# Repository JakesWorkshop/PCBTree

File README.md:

# PCBTree
A blinking Christmas Tree you can solder yourself

Tannenbaum.zip contains all Gerber files you'll need packed together into one 100 by 100 mm PCB. 
Note that this PCB contains 3 different desigs and some fabricators will charge extra for this

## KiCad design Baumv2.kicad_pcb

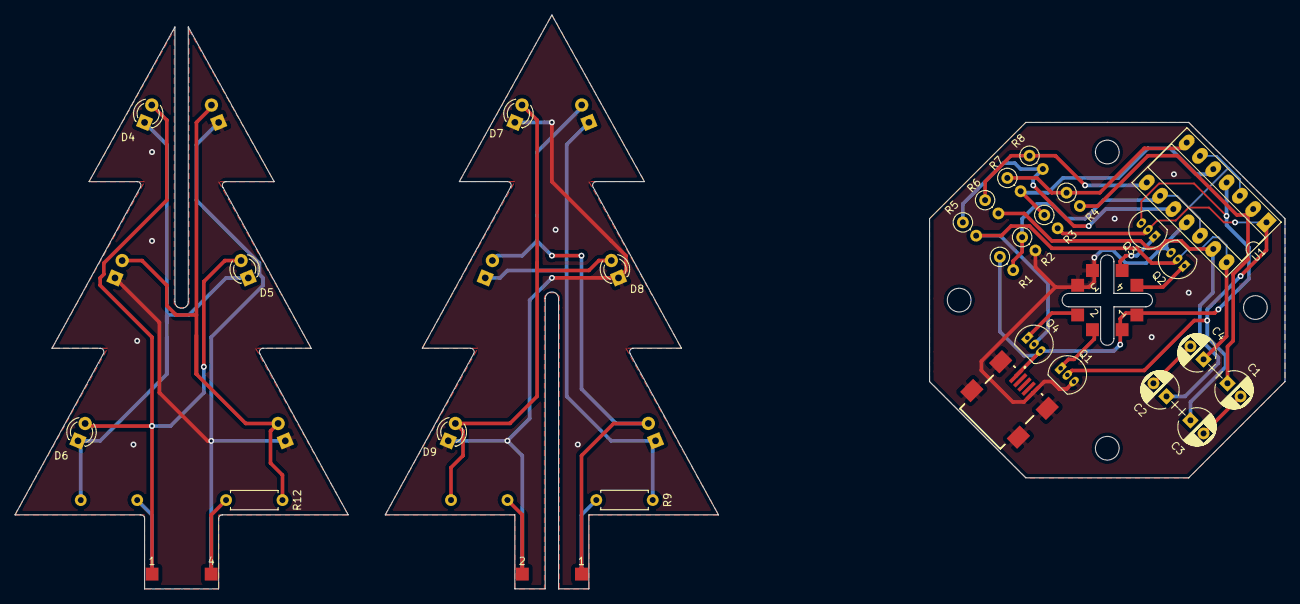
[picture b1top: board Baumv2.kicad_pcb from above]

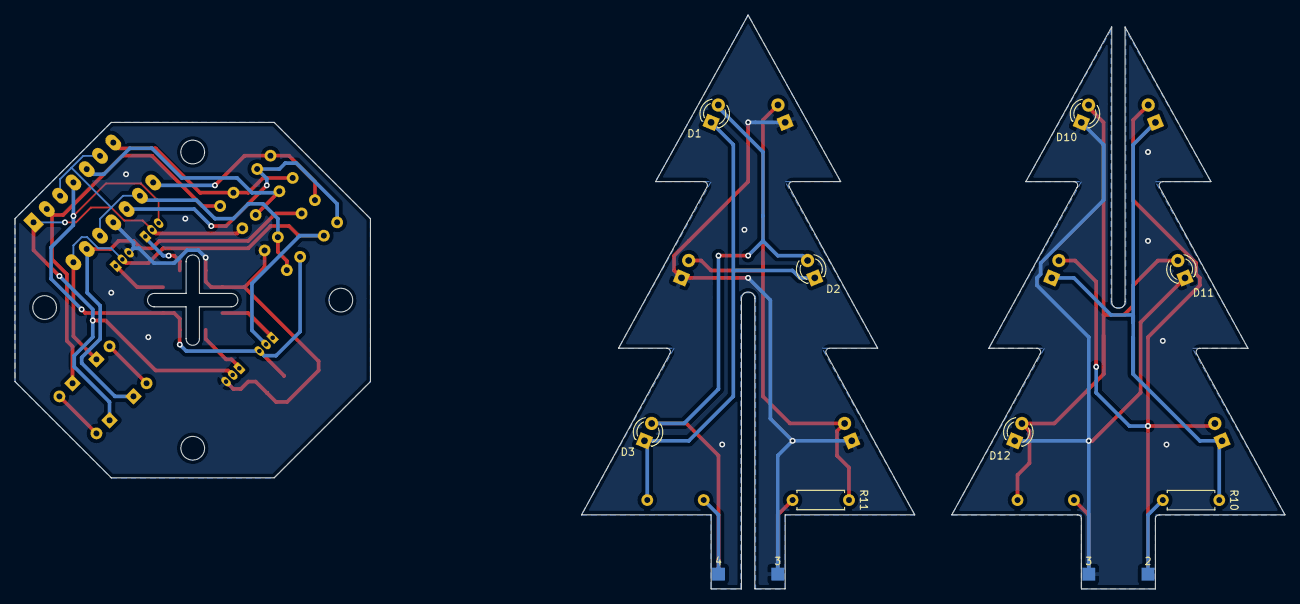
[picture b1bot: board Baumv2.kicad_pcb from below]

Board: 2 copper layers, 171.5 x 77.5 mm, 54 parts (12 on the bottom side), 6 nets.

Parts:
C1, C2, C3, C4: 10u; CP_Radial_D5.0mm_P2.50mm
D1, D2, D3, D4, D5, D6, D7, D8, D9, D10, D11, D12: LED; LED_D3.0mm
H1, H2, H3, H4: MountingHole; MountingHole_3.2mm_M3_DIN965
J1, J2, J3, J4, J5, J6, J7, J8, J10, J11, J12, J13, J14, J15, J16, J17: Conn_01x01_Female; Pinpad1
J9: USB2066-05-RBHM-15-STB-00-00-A; USB206605RBHM15STB0000A
Q1, Q2: 2N3906; TO-92_Inline_Narrow_Oval
Q3, Q4: 2N3904; TO-92_Inline_Narrow_Oval
R1, R2: 47k; R_Axial_DIN0207_L6.3mm_D2.5mm_P2.54mm_Vertical
R3, R5, R7, R8: 100k; R_Axial_DIN0207_L6.3mm_D2.5mm_P2.54mm_Vertical
R4, R6: 1M; R_Axial_DIN0207_L6.3mm_D2.5mm_P2.54mm_Vertical
R9, R10, R11, R12: R; R_Axial_DIN0207_L6.3mm_D2.5mm_P7.62mm_Horizontal
U1: LM324; DIP-14_W7.62mm_Socket_LongPads

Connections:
GND: D10.1, D11.1, D12.1, J7.1
unnamed: D4.1, D5.1, D6.1, R10.1
unnamed: D10.2, D11.2, D12.2, R12.2
VCC: D4.2, D5.2, D6.2, J13.1
sring2vcc: J17.1, R12.1
string1gnd: J1.1, R10.2

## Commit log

2021-12-03 Add files via upload
    Added KiCAD files and Gerber files as zip
2021-12-17 Add files via upload
    3d Model of the foot of the bottom PCB
